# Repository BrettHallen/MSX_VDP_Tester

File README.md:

# Yamaha V99x8 Tester for MSX
Simple Arduino sketch & PCB to test if a V9958 is real.<br>

PCB is designed & Arduino sketch generated (by Claude) but nothing is tested or sanity checked yet (3/Jul/2026).<br>

Idea is to query the "identification number" of the chip from bits 1-5 of status register S#1:
- 0 = V9938
- 1 = V9948
- 2 = V9958
- 3 = V9968
- 4 = V9978

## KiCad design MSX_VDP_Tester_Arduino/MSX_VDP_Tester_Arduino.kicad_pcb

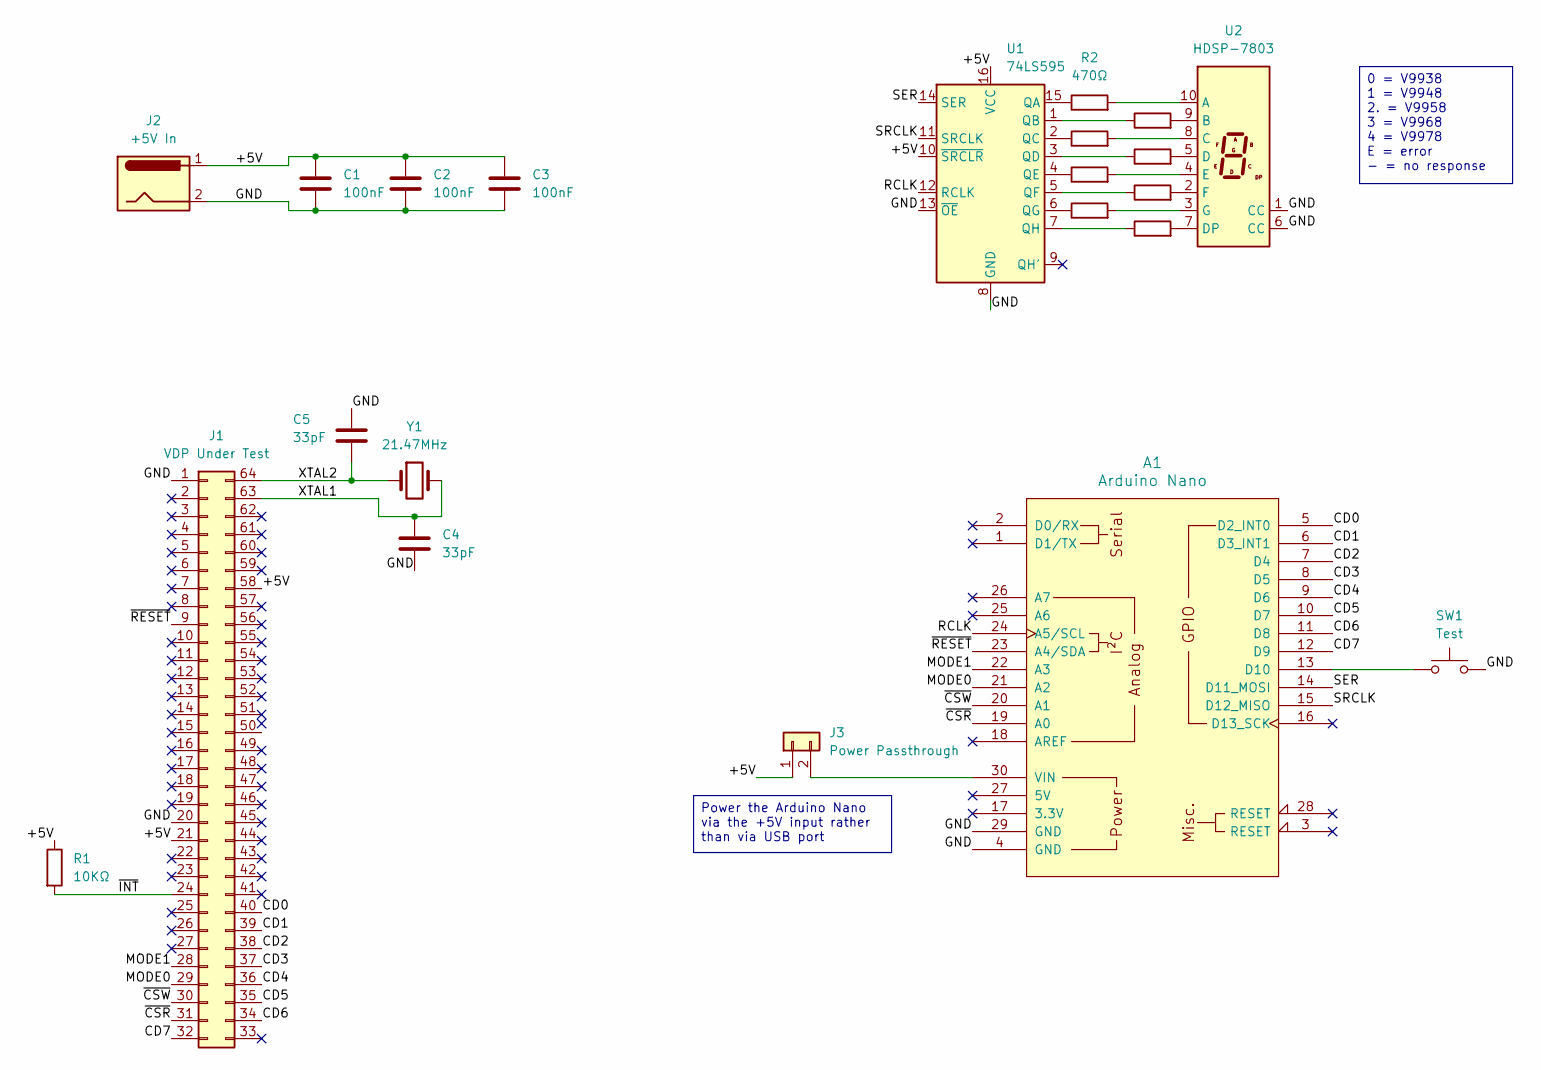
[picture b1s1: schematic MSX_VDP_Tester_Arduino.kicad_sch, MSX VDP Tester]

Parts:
A1: Arduino Nano; Arduino_Nano
C1, C2, C3: 100nF; C_Disc_D3.8mm_W2.6mm_P2.50mm
C4, C5: 33pF; C_Disc_D3.0mm_W1.6mm_P2.50mm
J1: VDP Under Test; DIPS1905W50P178L5730H420Q64N
J2: +5V In; BarrelJack_Horizontal
J3: Power Passthrough; PinHeader_1x02_P2.54mm_Vertical
R1: 10KΩ; R_Axial_DIN0207_L6.3mm_D2.5mm_P7.62mm_Horizontal
R2, R3, R4, R5, R6, R7, R8, R9: 470Ω; R_Axial_DIN0207_L6.3mm_D2.5mm_P7.62mm_Horizontal
SW1: Test; SW_PUSH_6mm
U1: 74LS595; DIP-16_W7.62mm
U2: HDSP-7803; HDSP-7801
Y1: 21.47MHz; Crystal_HC49-U_Vertical

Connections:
/+5V: C1.1, C2.1, C3.1, J1.21, J1.58, J2.1, J3.1, R1.1, U1.10 (~SRCLR), U1.16 (VCC)
/CD0: A1.5 (D2_INT0), J1.40
/CD1: A1.6 (D3_INT1), J1.39
/CD2: A1.7 (D4), J1.38
/CD3: A1.8 (D5), J1.37
/CD4: A1.9 (D6), J1.36
/CD5: A1.10 (D7), J1.35
/CD6: A1.11 (D8), J1.34
/CD7: A1.12 (D9), J1.32
/GND: A1.4 (GND), A1.29 (GND), C1.2, C2.2, C3.2, C4.2, C5.2, J1.1, J1.20, J2.2, SW1.2, U1.8 (GND), U1.13 (~OE), U2.1 (CC), U2.6 (CC)
/MODE0: A1.21 (A2), J1.29
/MODE1: A1.22 (A3), J1.28
/RCLK: A1.24 (A5/SCL), U1.12 (RCLK)
/SER: A1.14 (D11_MOSI), U1.14 (SER)
/SRCLK: A1.15 (D12_MISO), U1.11 (SRCLK)
/XTAL1: C4.1, J1.63, Y1.2
/XTAL2: C5.1, J1.64, Y1.1
/~CSR: A1.19 (A0), J1.31
/~CSW: A1.20 (A1), J1.30
/~INT: J1.24, R1.2
/~RESET: A1.23 (A4/SDA), J1.9
unnamed: A1.13 (D10), SW1.1
unnamed: A1.30 (VIN), J3.2
unnamed: R2.1, U1.15 (QA)
unnamed: R3.1, U1.1 (QB)
unnamed: R4.1, U1.2 (QC)
unnamed: R5.1, U1.3 (QD)
unnamed: R6.1, U1.4 (QE)
unnamed: R7.1, U1.5 (QF)
unnamed: R8.1, U1.6 (QG)
unnamed: R9.1, U1.7 (QH)
unnamed: R2.2, U2.10 (A)
unnamed: R3.2, U2.9 (B)
unnamed: R4.2, U2.8 (C)
unnamed: R5.2, U2.5 (D)
unnamed: R9.2, U2.7 (DP)
unnamed: R6.2, U2.4 (E)
unnamed: R7.2, U2.2 (F)
unnamed: R8.2, U2.3 (G)

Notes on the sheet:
Power the Arduino Nano via the +5V input rather than via USB port
0 = V9938 1 = V9948 2. = V9958 3 = V9968 4 = V9978 E = error - = no response

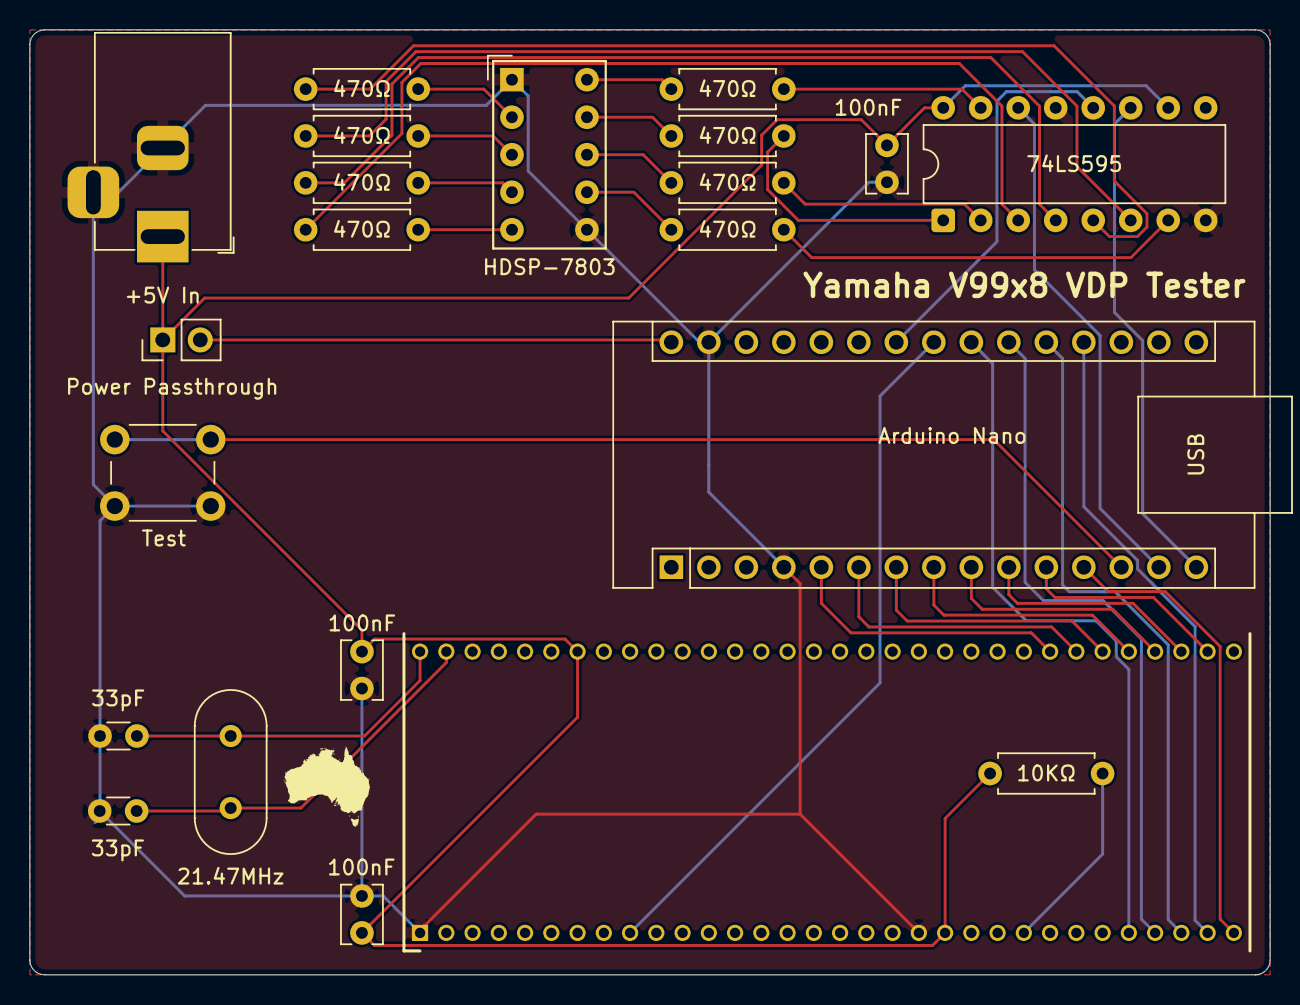
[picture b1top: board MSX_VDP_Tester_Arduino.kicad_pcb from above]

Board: 2 copper layers, 84.0 x 64.0 mm, 22 parts (0 on the bottom side), 39 nets.

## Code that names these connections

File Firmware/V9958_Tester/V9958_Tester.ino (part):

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 *    /RESET(9)->A4                       (strobes/mode/reset = PORTC 0..4)
 *    Button -> D10 to GND (internal pull-up)     LED -> D13 (onboard)
 *    7-seg via 74HC595 (pin names shown NXP / TI). Nano -> 595:
 *        D11 -> pin14  DS/SER    (serial data)
 *        D12 -> pin11  SHCP/SRCLK (shift clock)
 *        A5  -> pin12  STCP/RCLK  (latch)
 *    595 static pins: pin16 VCC->+5V   pin8 GND->GND
 *        pin13 /OE->GND (outputs enabled)   pin10 /MR->+5V (no reset)
 *        pin9 Q7S/QH' (serial-out) -> open (only used to chain a 2nd digit)
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 *    Display: 0-4 = VDP ID, DP lit = genuine V9958, '-' = no response,
 *        'E' = error (unstable or unrecognized ID).
 *    XTAL1(63) / XTAL2(64) -> clock: see CLOCK REQUIRED above (crystal across
 *        both pins, OR an oscillator module into XTAL1 with XTAL2 open)
 *    VDD(58)+VDD/DAC(21) -> +5V     GND(1)+GND/DAC(20) -> GND
 *    /INT(25), /WAIT(26), all VRAM/RGB/sync/color-bus pins -> open
 *
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// -------- PORTC bit positions for control lines (A0..A4) --------
// Order chosen to match the V9958 pin sequence (31,30,29,28) so the PCB
// traces run straight with no crossings/vias.
#define BIT_CSR    0   // A0  -> /CSR   (read strobe,  active LOW)
#define BIT_CSW    1   // A1  -> /CSW   (write strobe, active LOW)
#define BIT_MODE0  2   // A2  -> MODE0  (port-select bit 0)
#define BIT_MODE1  3   // A3  -> MODE1  (port-select bit 1)
#define BIT_RESET  4   // A4  -> /RESET (active LOW)

#define PIN_BUTTON 10  // PB2, INPUT_PULLUP
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// ============================================================

static inline void selectPort(uint8_t p) {
  // MODE0 = PC2 (port bit 0), MODE1 = PC3 (port bit 1); preserve CSR/CSW/RESET.
  PORTC = (PORTC & ~0x0C) | ((p & 0x03) << 2);
}

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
